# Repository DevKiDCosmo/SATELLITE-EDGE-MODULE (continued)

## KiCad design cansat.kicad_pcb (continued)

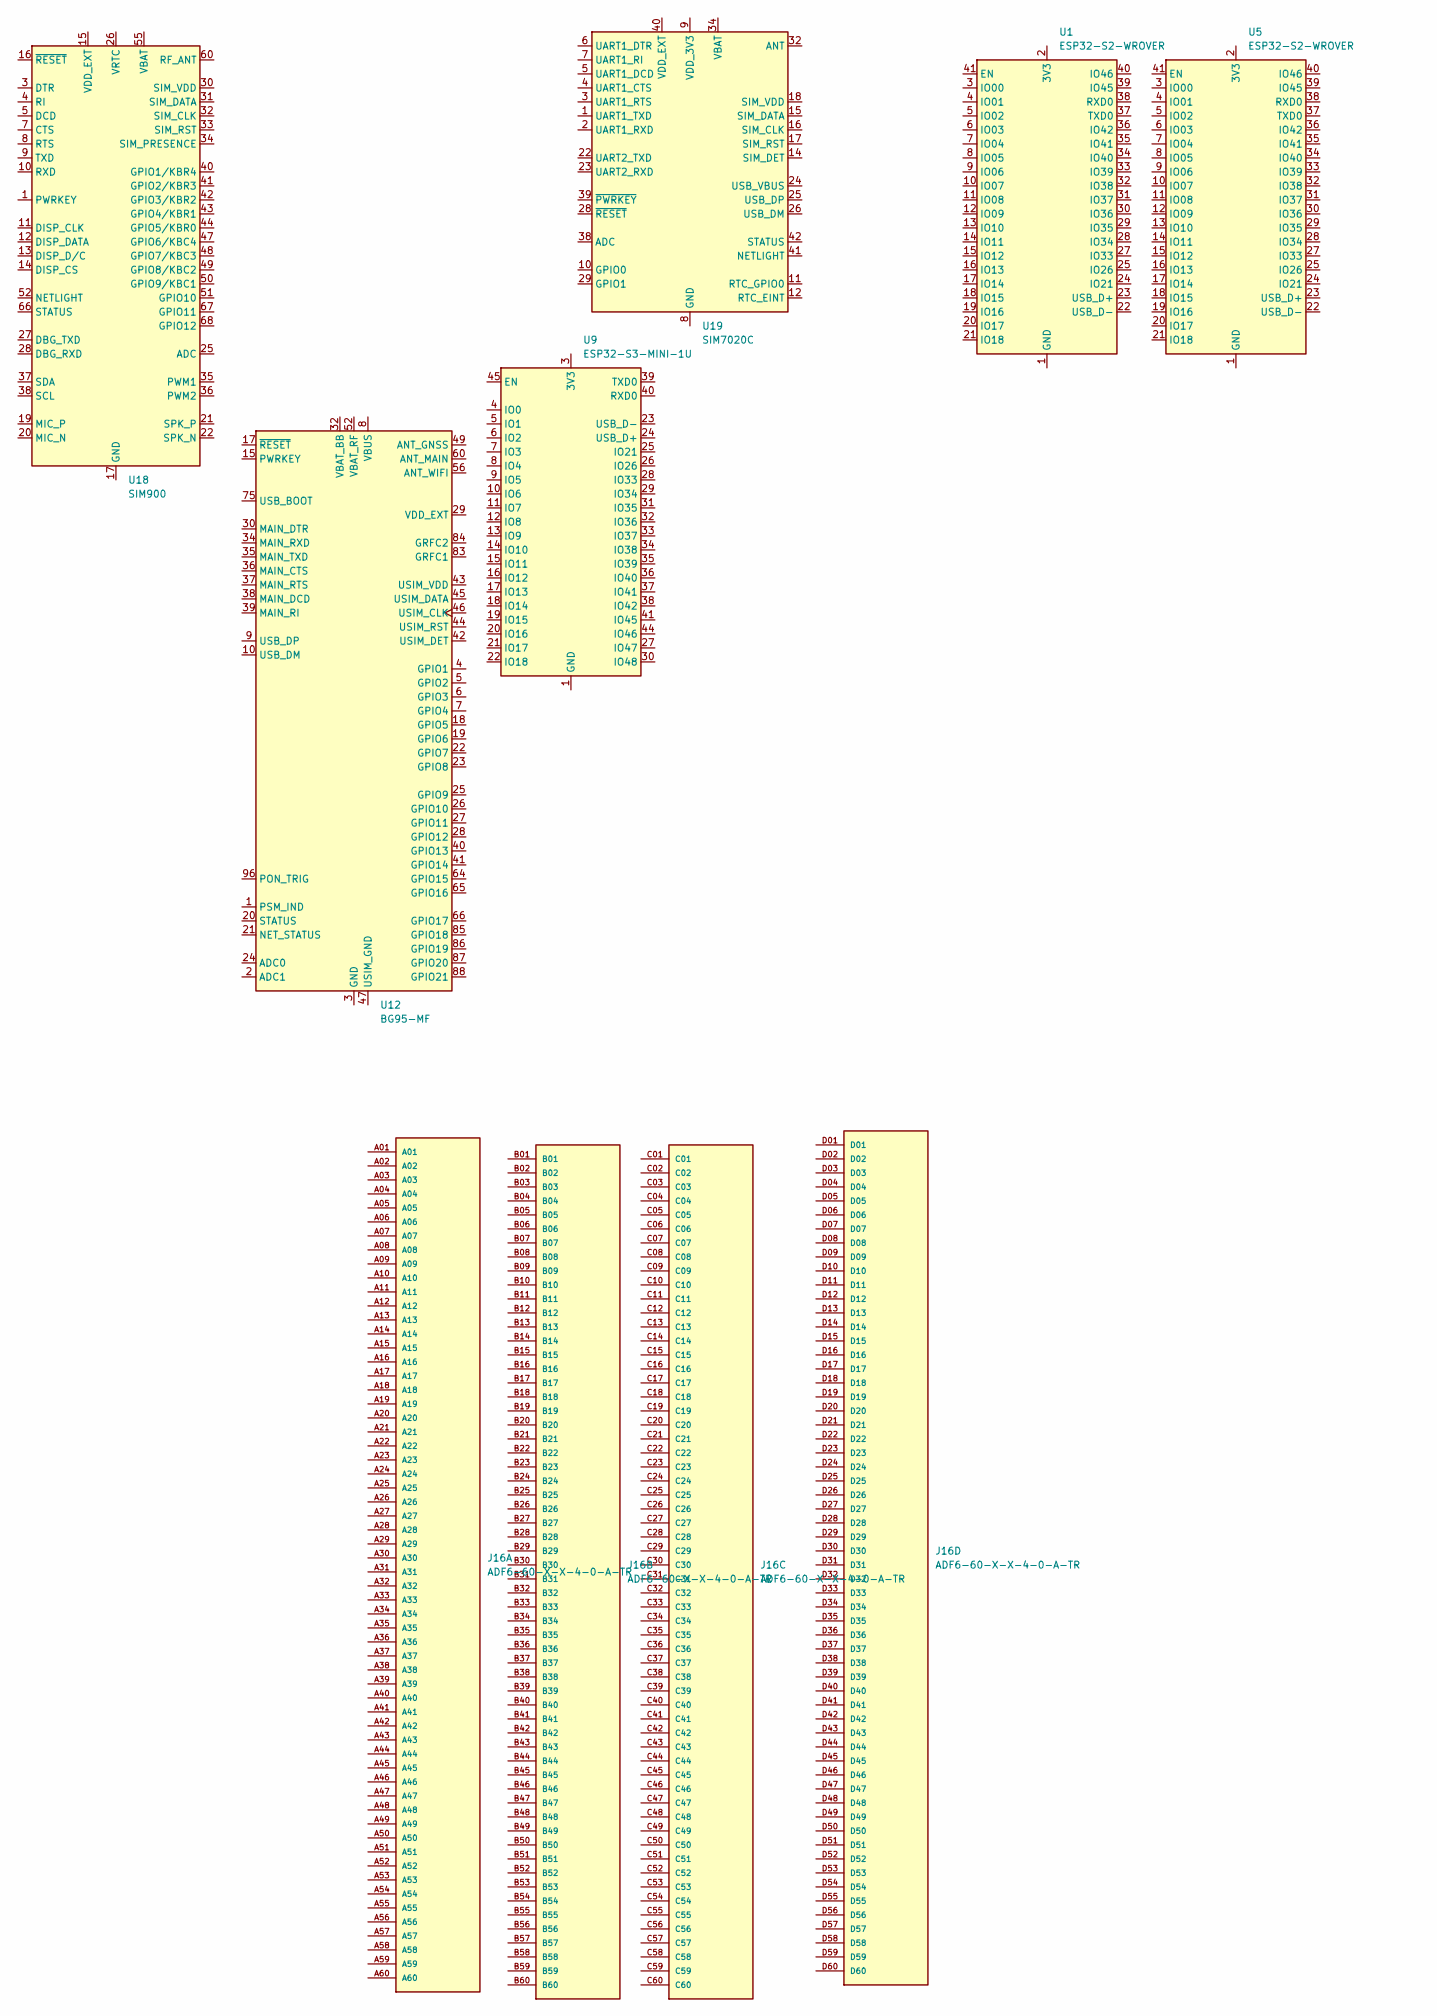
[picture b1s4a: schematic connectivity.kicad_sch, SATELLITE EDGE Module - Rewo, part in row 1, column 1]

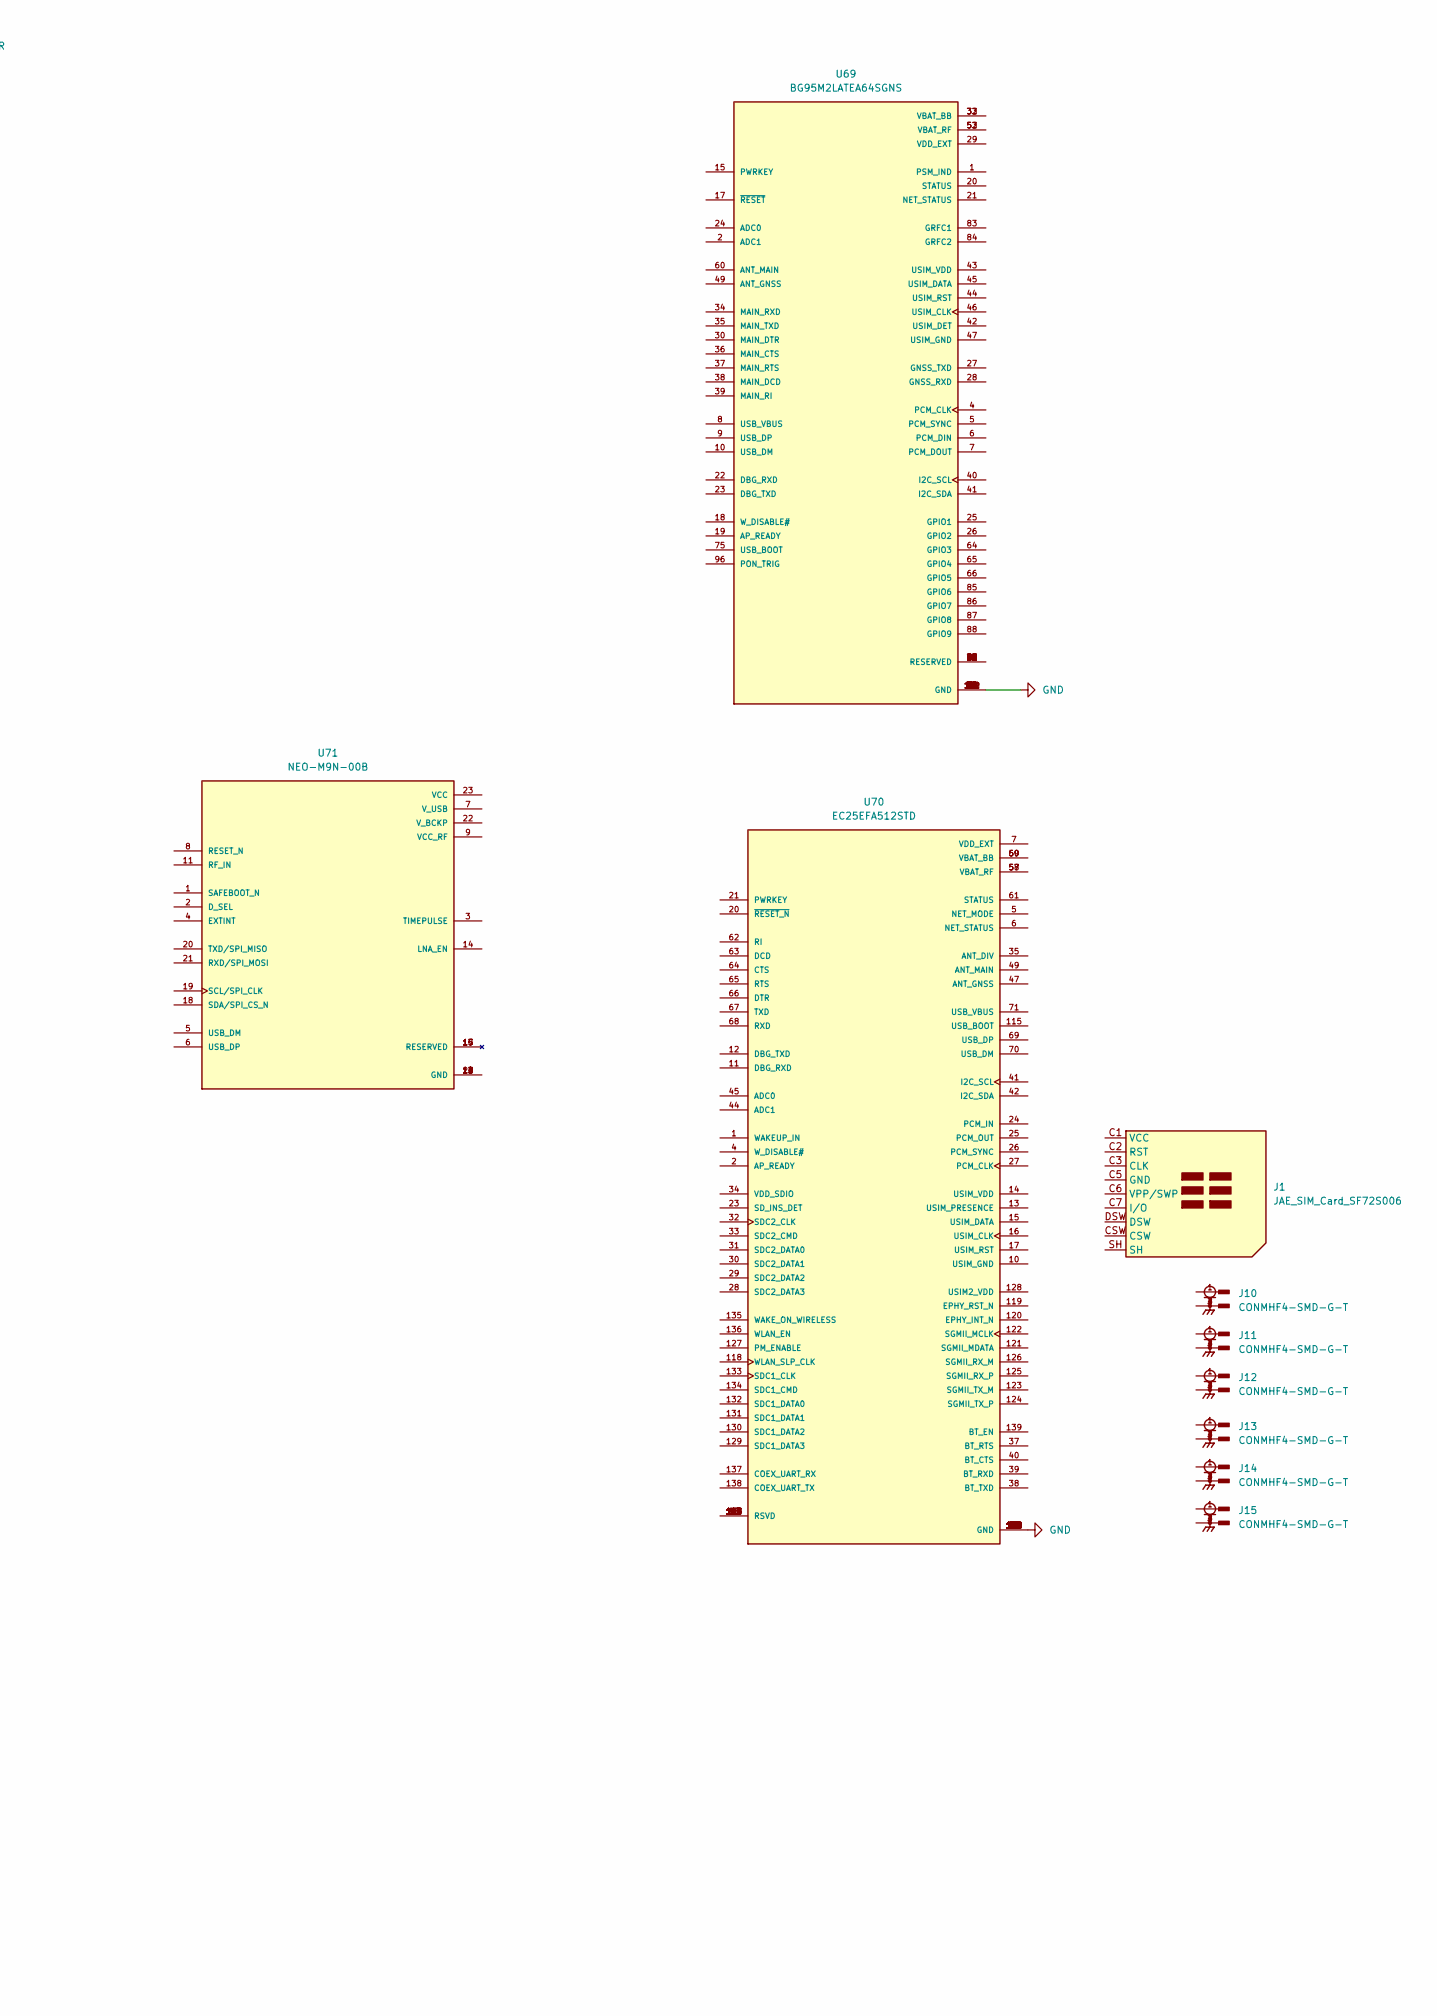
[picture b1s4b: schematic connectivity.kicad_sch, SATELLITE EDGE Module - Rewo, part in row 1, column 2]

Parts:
J1: JAE_SIM_Card_SF72S006
J10, J11, J12, J13, J14, J15: CONMHF4-SMD-G-T; TE_CONMHF4-SMD-G-T; PARTREV A
J16: ADF6-60-X-X-4-0-A-TR; SAMTEC_ADF6-60-X-X-4-0-A-TR; PARTREV E
U1, U5: ESP32-S2-WROVER
U9: ESP32-S3-MINI-1U; ESP32-S2-MINI-1U
U12: BG95-MF; Quectel_BG95
U18: SIM900; SIMCom_SIM900
U19: SIM7020C; SIMCom_SIM800C
U69: BG95M2LATEA64SGNS; XCVR_BG95M2LATEA64SGNS
U70: EC25EFA512STD; XCVR_EC25EFA512STD
U71: NEO-M9N-00B; XCVR_NEO-M9N-00B; PARTREV R05

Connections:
GND: U69.3 (GND), U69.31 (GND), U69.48 (GND), U69.50 (GND), U69.54 (GND), U69.55 (GND), U69.58 (GND), U69.59 (GND), U69.61 (GND), U69.62 (GND), U69.67 (GND), U69.68 (GND), U69.69 (GND), U69.70 (GND), U69.71 (GND), U69.72 (GND), U69.73 (GND), U69.74 (GND), U69.79 (GND), U69.80 (GND), U69.81 (GND), U69.82 (GND), U69.89 (GND), U69.90 (GND), U69.91 (GND), U69.100 (GND), U69.101 (GND), U69.102 (GND), U70.8 (GND), U70.9 (GND), U70.19 (GND), U70.22 (GND), U70.36 (GND), U70.46 (GND), U70.48 (GND), U70.50 (GND), U70.51 (GND), U70.52 (GND), U70.53 (GND), U70.54 (GND), U70.56 (GND), U70.72 (GND), U70.85 (GND), U70.86 (GND), U70.87 (GND), U70.88 (GND), U70.89 (GND), U70.90 (GND), U70.91 (GND), U70.92 (GND), U70.93 (GND), U70.94 (GND), U70.95 (GND), U70.96 (GND), U70.97 (GND), U70.98 (GND), U70.99 (GND), U70.100 (GND), U70.101 (GND), U70.102 (GND), U70.103 (GND), U70.104 (GND), U70.105 (GND), U70.106 (GND), U70.107 (GND), U70.108 (GND), U70.109 (GND), U70.110 (GND), U70.111 (GND), U70.112 (GND); also elsewhere on the board
unnamed: J10.2, J10.3, J10.4
unnamed: J11.2, J11.3, J11.4
unnamed: J12.2, J12.3, J12.4
unnamed: J13.2, J13.3, J13.4
unnamed: J14.2, J14.3, J14.4
unnamed: J15.2, J15.3, J15.4
unnamed: U1.1 (GND), U1.26 (GND), U1.42 (GND), U1.43 (GND)
unnamed: U5.1 (GND), U5.26 (GND), U5.42 (GND), U5.43 (GND)
unnamed: U9.1 (GND), U9.2 (GND), U9.42 (GND), U9.43 (GND), U9.46 (GND), U9.47 (GND), U9.48 (GND), U9.49 (GND), U9.50 (GND), U9.51 (GND), U9.52 (GND), U9.53 (GND), U9.54 (GND), U9.55 (GND), U9.56 (GND), U9.57 (GND), U9.58 (GND), U9.59 (GND), U9.60 (GND), U9.61 (GND), U9.62 (GND), U9.63 (GND), U9.64 (GND), U9.65 (GND)
unnamed: U12.3 (GND), U12.31 (GND), U12.48 (GND), U12.50 (GND), U12.54 (GND), U12.55 (GND), U12.58 (GND), U12.59 (GND), U12.61 (GND), U12.62 (GND), U12.67 (GND), U12.68 (GND), U12.69 (GND), U12.70 (GND), U12.71 (GND), U12.72 (GND), U12.73 (GND), U12.74 (GND), U12.79 (GND), U12.80 (GND), U12.81 (GND), U12.82 (GND), U12.89 (GND), U12.90 (GND), U12.91 (GND), U12.100 (GND), U12.101 (GND), U12.102 (GND)
unnamed: U12.32 (VBAT_BB), U12.33 (VBAT_BB)
unnamed: U12.52 (VBAT_RF), U12.53 (VBAT_RF)
unnamed: U18.17 (GND), U18.18 (GND), U18.29 (GND), U18.39 (GND), U18.45 (GND), U18.46 (GND), U18.53 (GND), U18.54 (GND), U18.58 (GND), U18.59 (GND), U18.61 (GND), U18.62 (GND), U18.63 (GND), U18.64 (GND), U18.65 (GND)
unnamed: U18.55 (VBAT), U18.56 (VBAT), U18.57 (VBAT)
unnamed: U19.8 (GND), U19.13 (GND), U19.19 (GND), U19.21 (GND), U19.27 (GND), U19.30 (GND), U19.31 (GND), U19.33 (GND), U19.36 (GND), U19.37 (GND)
unnamed: U19.34 (VBAT), U19.35 (VBAT)
unnamed: U69.11 (RESERVED), U69.12 (RESERVED), U69.13 (RESERVED), U69.14 (RESERVED), U69.16 (RESERVED), U69.51 (RESERVED), U69.56 (RESERVED), U69.57 (RESERVED), U69.63 (RESERVED), U69.76 (RESERVED), U69.77 (RESERVED), U69.78 (RESERVED), U69.92 (RESERVED), U69.93 (RESERVED), U69.94 (RESERVED), U69.95 (RESERVED), U69.97 (RESERVED), U69.98 (RESERVED), U69.99 (RESERVED)
unnamed: U69.32 (VBAT_BB), U69.33 (VBAT_BB)
unnamed: U69.52 (VBAT_RF), U69.53 (VBAT_RF)
unnamed: U70.3 (RSVD), U70.18 (RSVD), U70.43 (RSVD), U70.55 (RSVD), U70.113 (RSVD), U70.114 (RSVD), U70.116 (RSVD), U70.117 (RSVD), U70.140 (RSVD), U70.141 (RSVD), U70.142 (RSVD), U70.143 (RSVD), U70.144 (RSVD)
unnamed: U70.59 (VBAT_BB), U70.60 (VBAT_BB)
unnamed: U70.57 (VBAT_RF), U70.58 (VBAT_RF)
unnamed: U71.10 (GND), U71.12 (GND), U71.13 (GND), U71.24 (GND)

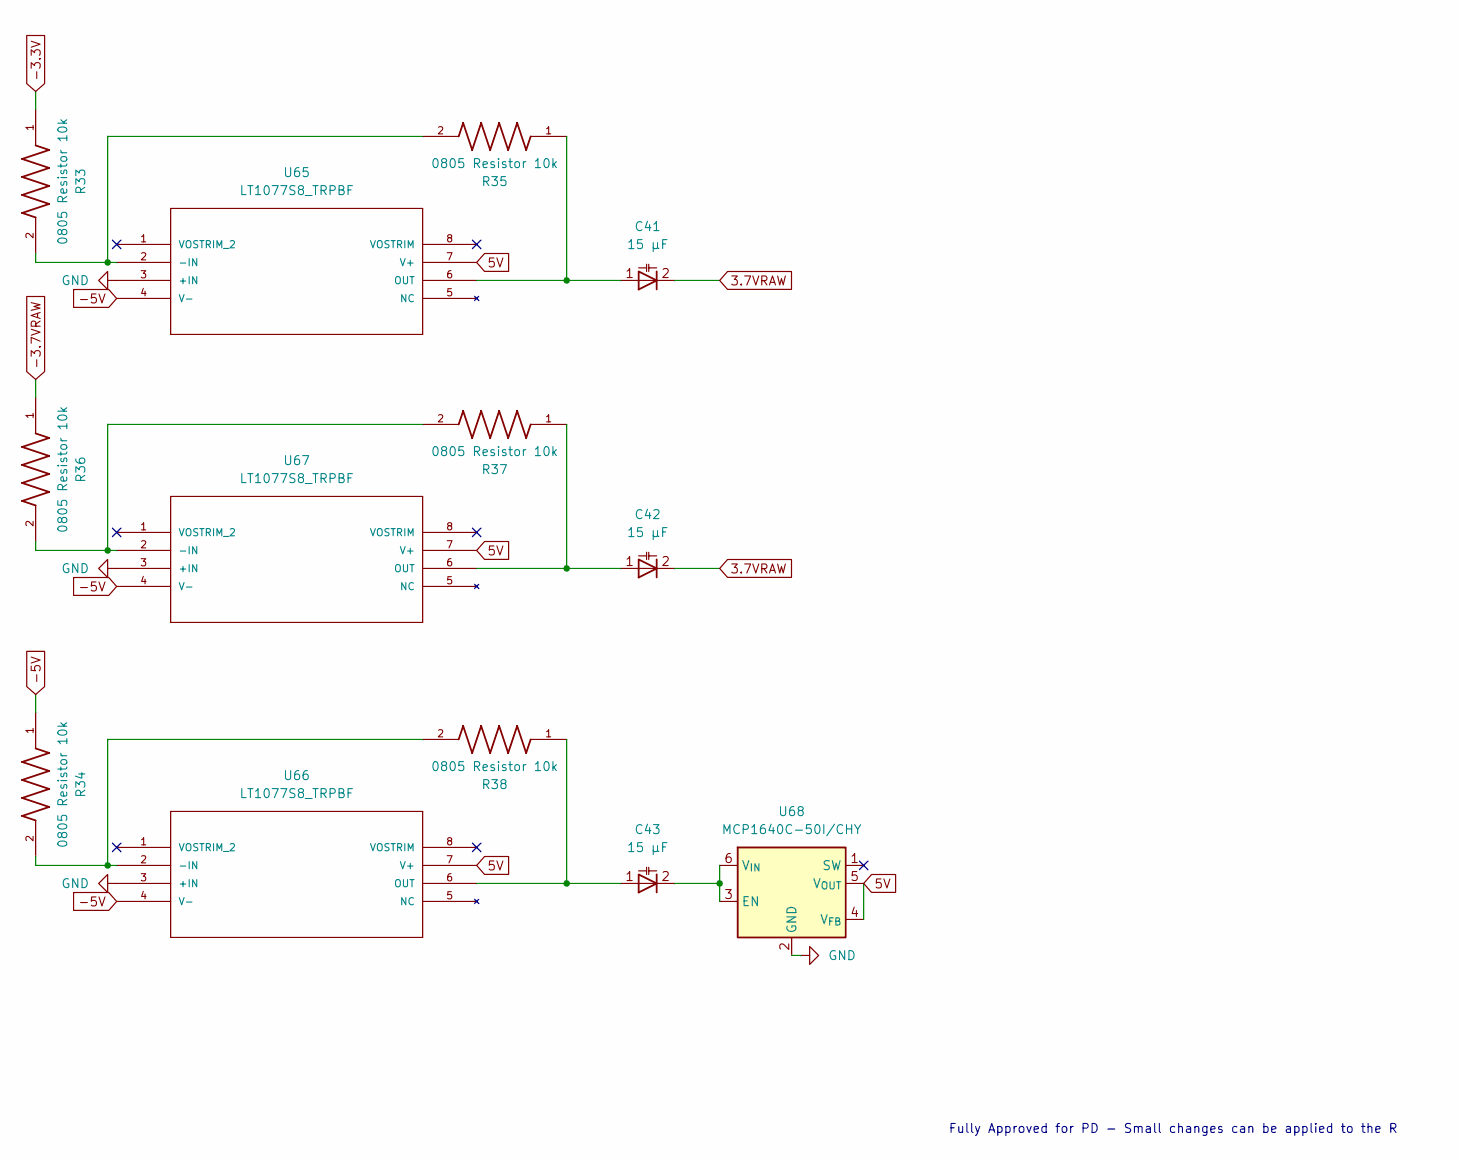
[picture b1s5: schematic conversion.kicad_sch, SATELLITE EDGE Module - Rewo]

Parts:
C41, C42, C43: 15 µF; C_0603_1608Metric
R33, R34, R35, R36, R37, R38: 0805 Resistor 10k; R_0805_2012Metric
U65, U66, U67: LT1077S8_TRPBF; SO-8_S; MANUFACTURER_PART_NUMBER lt1077s8
U68: MCP1640C-50I/CHY; SOT-23-6

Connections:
3.7VRAW: C41.2, C42.2; also elsewhere on the board
5V: U65.7 (V+), U66.7 (V+), U67.7 (V+), U68.4 (V_{FB}), U68.5 (V_{OUT}); also elsewhere on the board
-3.3V: R33.1; also elsewhere on the board
-3.7VRAW: R36.1; also elsewhere on the board
-5V: R34.1, U65.4 (V-), U66.4 (V-), U67.4 (V-)
GND: U65.3 (+IN), U66.3 (+IN), U67.3 (+IN), U68.2 (GND); also elsewhere on the board
unnamed: R33.2, R35.2, U65.2 (-IN)
unnamed: C41.1, R35.1, U65.6 (OUT)
unnamed: R34.2, R38.2, U66.2 (-IN)
unnamed: C43.1, R38.1, U66.6 (OUT)
unnamed: R36.2, R37.2, U67.2 (-IN)
unnamed: C42.1, R37.1, U67.6 (OUT)
unnamed: C43.2, U68.3 (EN), U68.6 (V_{IN})

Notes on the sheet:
Fully Approved for PD - Small changes can be applied to the R

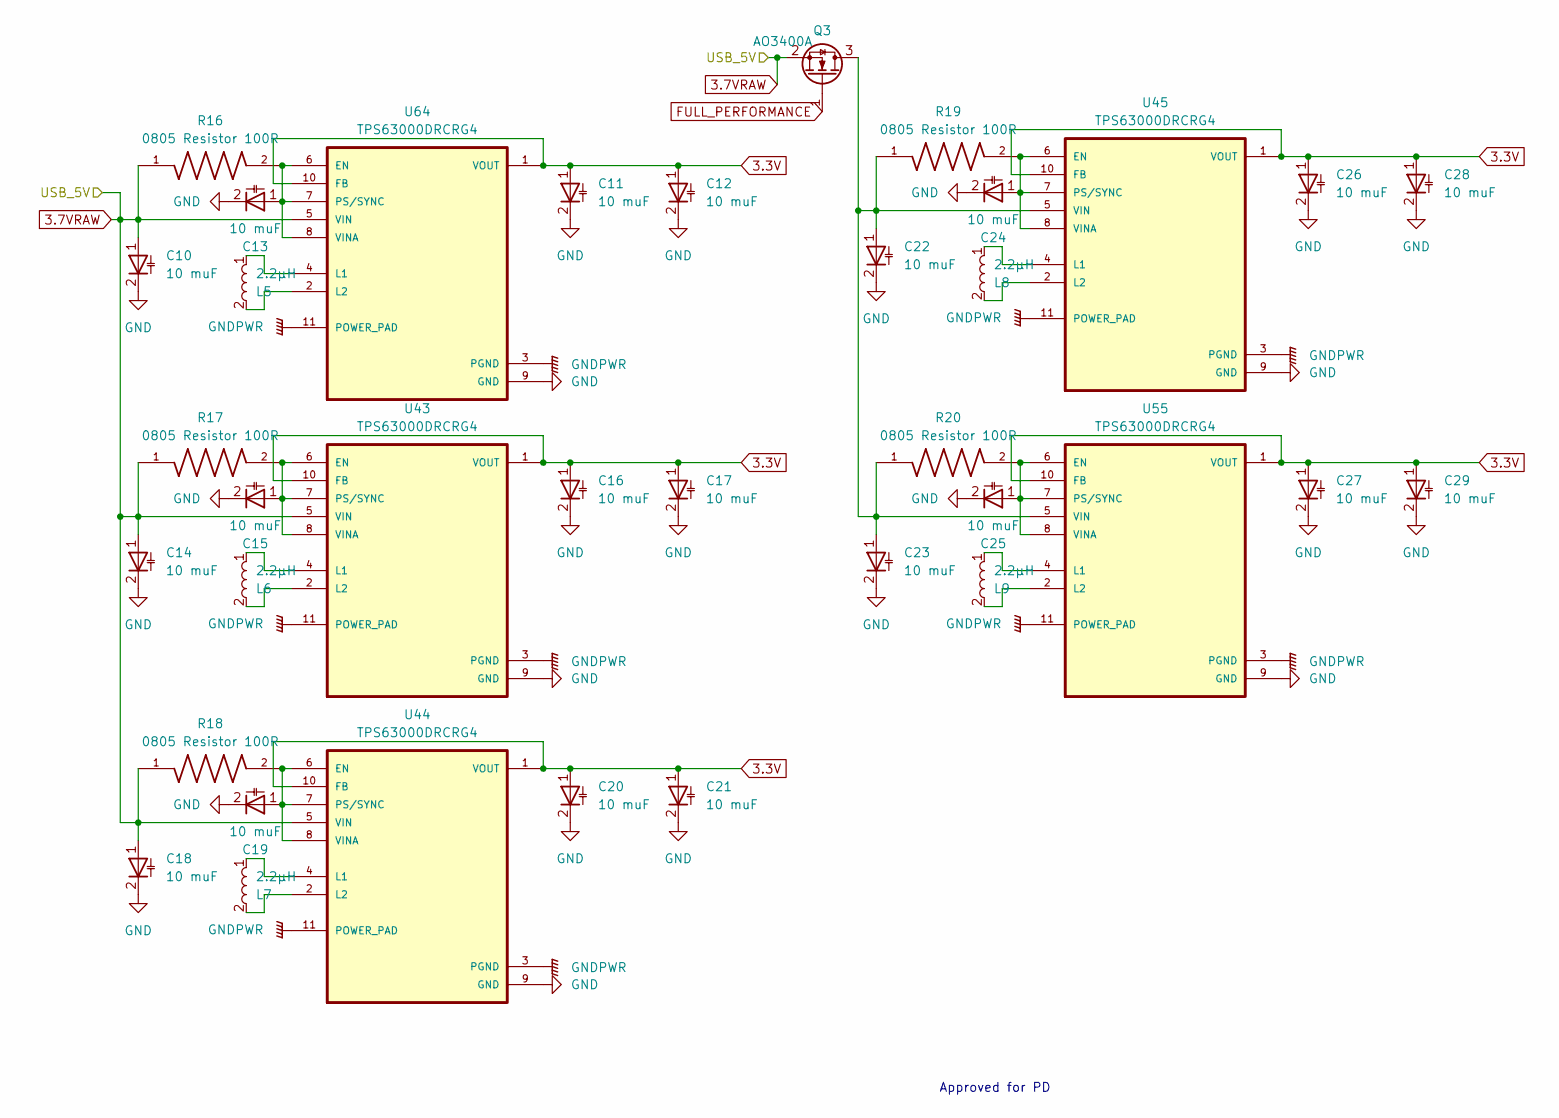
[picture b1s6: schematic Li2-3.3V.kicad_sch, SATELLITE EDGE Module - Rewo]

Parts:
C10, C11, C12, C13, C14, C15, C16, C17, C18, C19, C20, C21, C22, C23, C24, C25, C26, C27, C28, C29: 10 muF; C_0805_2012Metric
L5, L6, L7, L8, L9: 2.2µH; L_0805_2012Metric
Q3: AO3400A; SOT-23
R16, R17, R18, R19, R20: 0805 Resistor 100R; R_0805_2012Metric
U43, U44, U45, U55, U64: TPS63000DRCRG4; VREG_V62_16624-01YE

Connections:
3.3V: C11.1, C12.1, C16.1, C17.1, C20.1, C21.1, C26.1, C27.1, C28.1, C29.1, U43.1 (VOUT), U43.10 (FB), U44.1 (VOUT), U44.10 (FB), U45.1 (VOUT), U45.10 (FB), U55.1 (VOUT), U55.10 (FB), U64.1 (VOUT), U64.10 (FB); also elsewhere on the board
3.7VRAW: C10.1, C14.1, C18.1, Q3.2 (S), R16.1, R17.1, R18.1, U43.5 (VIN), U44.5 (VIN), U64.5 (VIN); also elsewhere on the board
FULL_PERFORMANCE: Q3.1 (G); also elsewhere on the board
GND: C10.2, C11.2, C12.2, C13.2, C14.2, C15.2, C16.2, C17.2, C18.2, C19.2, C20.2, C21.2, C22.2, C23.2, C24.2, C25.2, C26.2, C27.2, C28.2, C29.2, U43.9 (GND), U44.9 (GND), U45.9 (GND), U55.9 (GND), U64.9 (GND); also elsewhere on the board
GNDPWR: U43.3 (PGND), U43.11 (POWER_PAD), U44.3 (PGND), U44.11 (POWER_PAD), U45.3 (PGND), U45.11 (POWER_PAD), U55.3 (PGND), U55.11 (POWER_PAD), U64.3 (PGND), U64.11 (POWER_PAD); also elsewhere on the board
unnamed: C22.1, C23.1, Q3.3 (D), R19.1, R20.1, U45.5 (VIN), U55.5 (VIN)
unnamed: C15.1, R17.2, U43.6 (EN), U43.7 (PS/SYNC), U43.8 (VINA)
unnamed: L6.1, U43.4 (L1)
unnamed: L6.2, U43.2 (L2)
unnamed: C19.1, R18.2, U44.6 (EN), U44.7 (PS/SYNC), U44.8 (VINA)
unnamed: L7.1, U44.4 (L1)
unnamed: L7.2, U44.2 (L2)
unnamed: C24.1, R19.2, U45.6 (EN), U45.7 (PS/SYNC), U45.8 (VINA)
unnamed: L8.1, U45.4 (L1)
unnamed: L8.2, U45.2 (L2)
unnamed: C25.1, R20.2, U55.6 (EN), U55.7 (PS/SYNC), U55.8 (VINA)
unnamed: L9.1, U55.4 (L1)
unnamed: L9.2, U55.2 (L2)
unnamed: C13.1, R16.2, U64.6 (EN), U64.7 (PS/SYNC), U64.8 (VINA)
unnamed: L5.1, U64.4 (L1)
unnamed: L5.2, U64.2 (L2)

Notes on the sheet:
Approved for PD

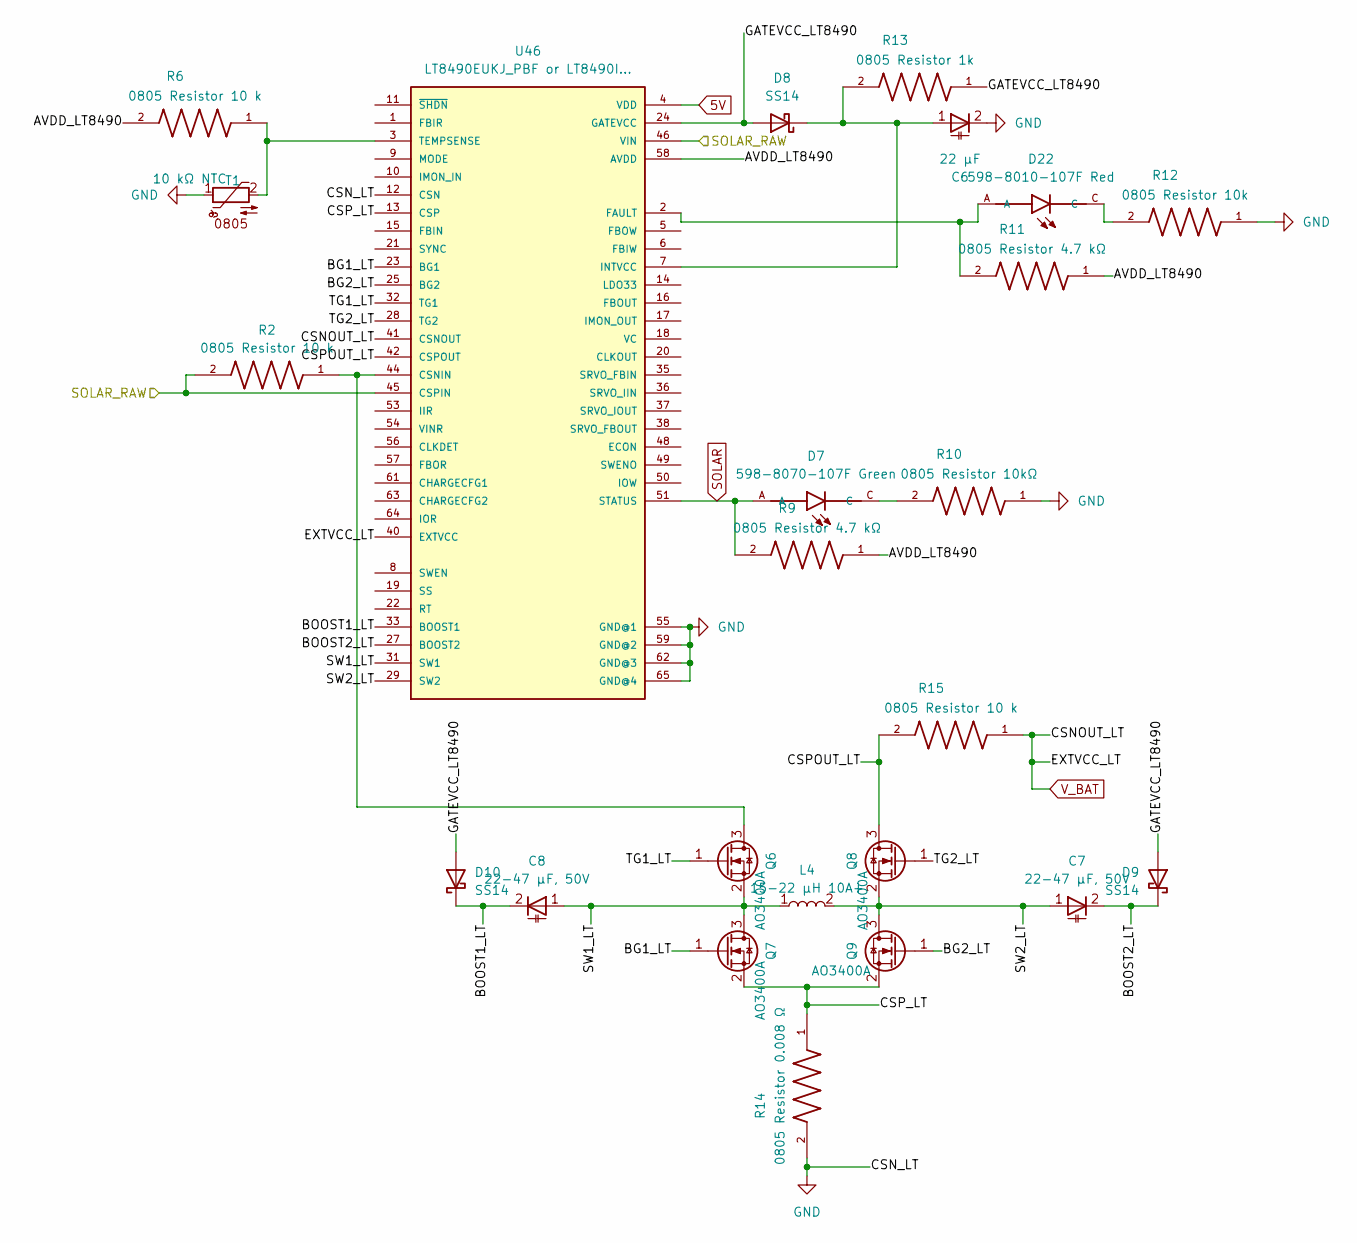
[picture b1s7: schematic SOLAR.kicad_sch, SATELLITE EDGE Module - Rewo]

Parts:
C6: 22 µF; C_0603_1608Metric
C7, C8: 22-47 µF, 50V; C_0603_1608Metric
D7: 598-8070-107F Green; LEDSC160X80X70L45N
D8, D9, D10: SS14; D_SMA
D22: 598-8010-107F Red; LEDSC160X80X70L45N
L4: 15-22 µH 10A+; L_0805_2012Metric
Q6, Q7, Q8, Q9: AO3400A; SOT-23
R2, R6, R15: 0805 Resistor 10 k; R_0805_2012Metric
R9, R11: 0805 Resistor 4.7 kΩ; R_0805_2012Metric
R10: 0805 Resistor 10kΩ; R_0805_2012Metric
R12: 0805 Resistor 10k; R_0805_2012Metric
R13: 0805 Resistor 1k; R_0805_2012Metric
R14: 0805 Resistor 0.008 Ω; R_0805_2012Metric
T1: 10 kΩ NTC; C_0805_2012Metric
U46: LT8490EUKJ_PBF or LT8490I...; QFN50P700X1100X80-65N

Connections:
5V: U46.4 (VDD); also elsewhere on the board
/Energy/SOLAR/AVDD_LT8490: R6.2, R9.1, R11.1, U46.58 (AVDD)
/Energy/SOLAR/BG1_LT: Q7.1 (G), U46.23 (BG1)
/Energy/SOLAR/BG2_LT: Q9.1 (G), U46.25 (BG2)
/Energy/SOLAR/BOOST1_LT: C8.2, D10.1 (K), U46.33 (BOOST1)
/Energy/SOLAR/BOOST2_LT: C7.2, D9.1 (K), U46.27 (BOOST2)
/Energy/SOLAR/CSPOUT_LT: Q8.3 (D), R15.2, U46.42 (CSPOUT)
/Energy/SOLAR/CSP_LT: Q7.2 (S), Q9.2 (S), R14.1, U46.13 (CSP)
/Energy/SOLAR/GATEVCC_LT8490: D8.2 (A), D9.2 (A), D10.2 (A), R13.1, U46.24 (GATEVCC)
/Energy/SOLAR/SOLAR_RAW: R2.2, U46.45 (CSPIN), U46.46 (VIN); also elsewhere on the board
/Energy/SOLAR/SW1_LT: C8.1, L4.1, Q6.2 (S), Q7.3 (D), U46.31 (SW1)
/Energy/SOLAR/SW2_LT: C7.1, L4.2, Q8.2 (S), Q9.3 (D), U46.29 (SW2)
/Energy/SOLAR/TG1_LT: Q6.1 (G), U46.32 (TG1)
/Energy/SOLAR/TG2_LT: Q8.1 (G), U46.28 (TG2)
GND: C6.2, R10.1, R12.1, R14.2, T1.1, U46.12 (CSN), U46.55 (GND@1), U46.59 (GND@2), U46.62 (GND@3), U46.65 (GND@4); also elsewhere on the board
unnamed: D7.C, R10.2
unnamed: C6.1, D8.1 (K), R13.2, U46.7 (INTVCC)
unnamed: D22.C, R12.2
unnamed: Q6.3 (D), R2.1, U46.44 (CSNIN)
unnamed: D22.A, R11.2, U46.2 (FAULT)
unnamed: R6.1, T1.2, U46.3 (TEMPSENSE)
SOLAR: D7.A, R9.2, U46.51 (STATUS); also elsewhere on the board
V_BAT: R15.1, U46.40 (EXTVCC), U46.41 (CSNOUT); also elsewhere on the board

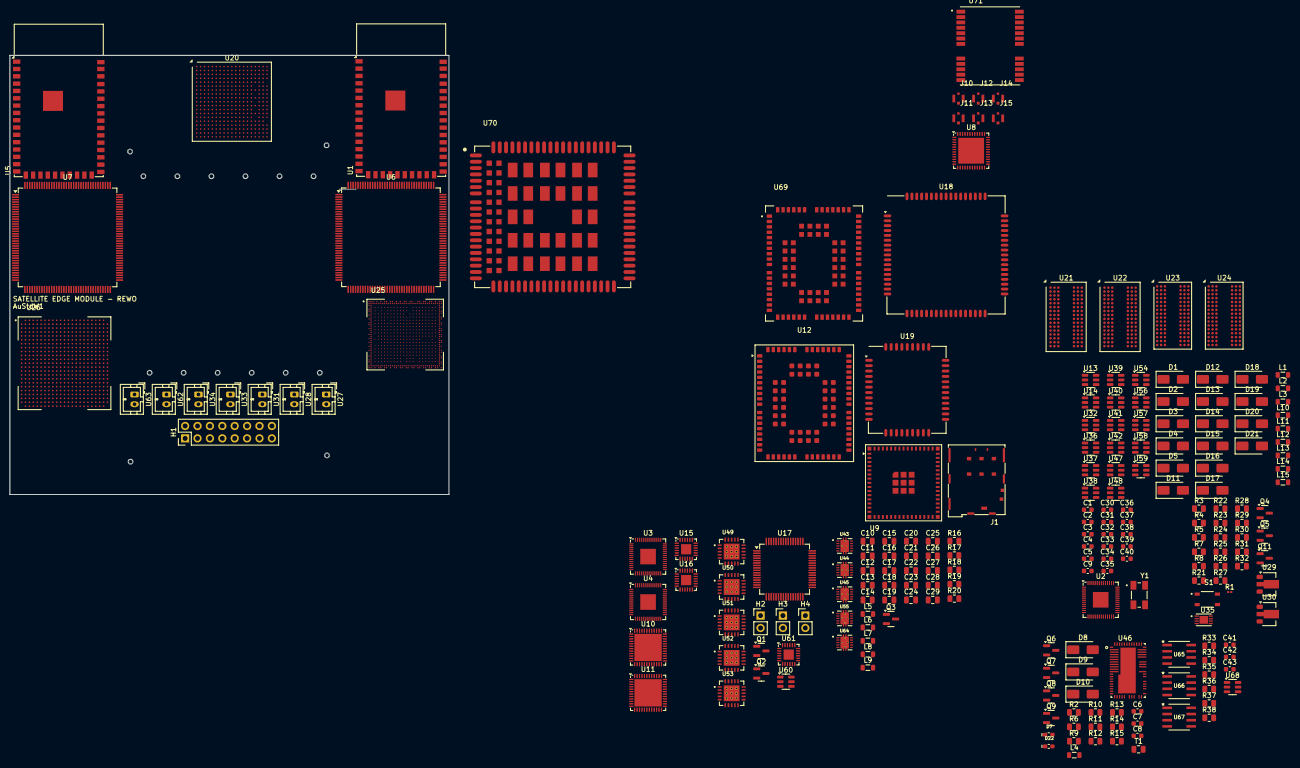
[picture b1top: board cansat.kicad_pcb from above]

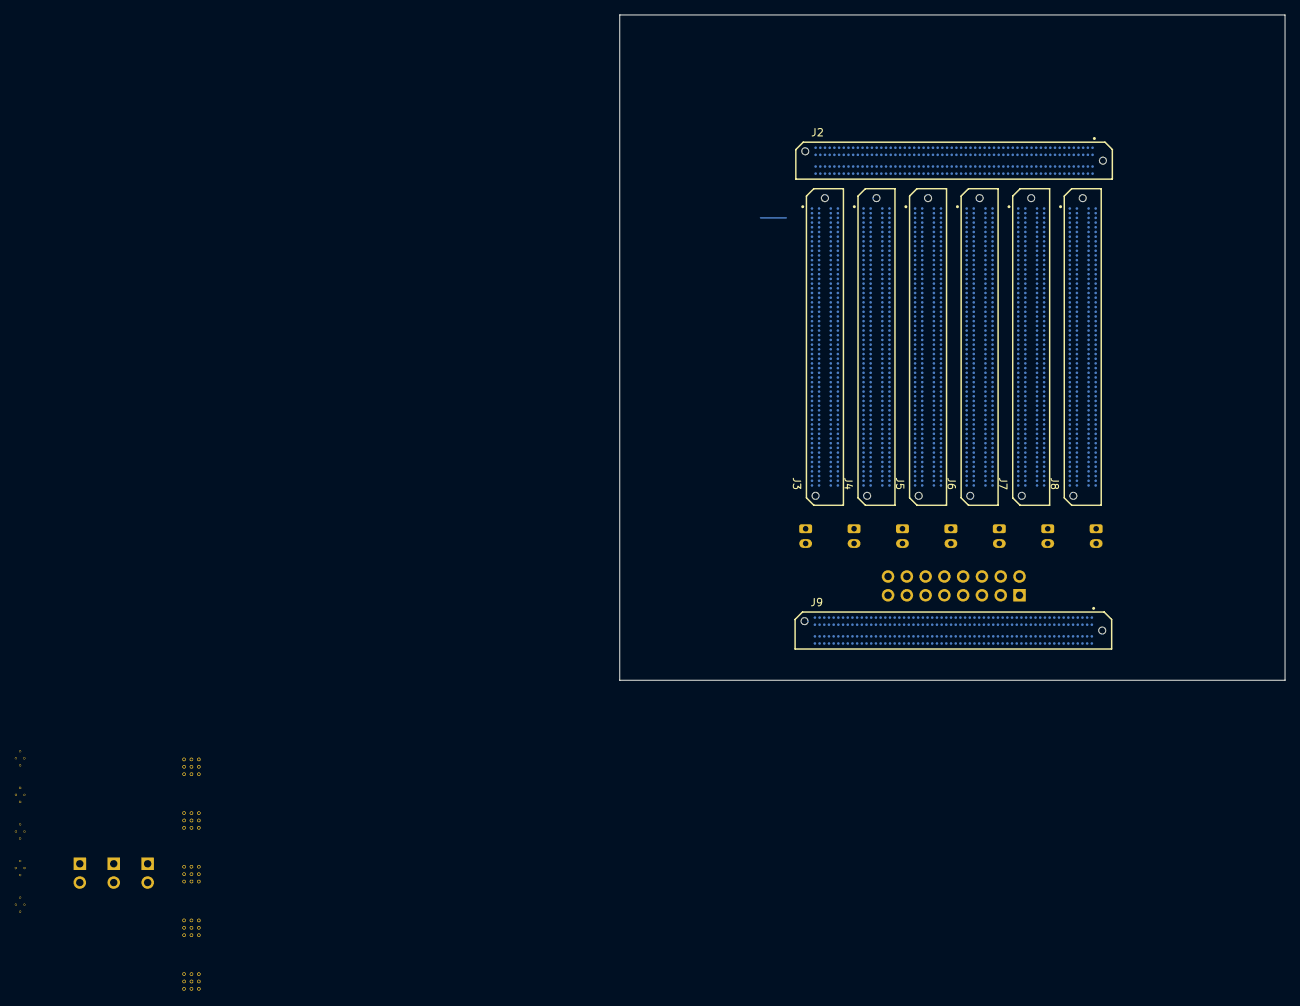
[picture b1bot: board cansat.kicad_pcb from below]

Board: 6 copper layers, 90.0 x 90.0 mm, 220 parts (8 on the bottom side), 201 nets.

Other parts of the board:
U8: ESP32-PICO-V3; QFN-48-1EP_7x7mm_P0.5mm_EP5.3x5.3mm

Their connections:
unnamed: U8.3 (VDDA3P3), U8.4 (VDDA3P3)
unnamed: U8.1 (VDDA), U8.43 (VDDA), U8.46 (VDDA)

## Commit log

2025-08-11 INIT
2025-08-11 Important
